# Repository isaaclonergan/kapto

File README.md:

# kapto
Framework to convert a 3D printer into an affordable pick and place machine.

# sammich
Interpreter board for Creality 4.2.7 motherboard. Plugs directly into display port and will convert to RS-485 for the feeder modules.

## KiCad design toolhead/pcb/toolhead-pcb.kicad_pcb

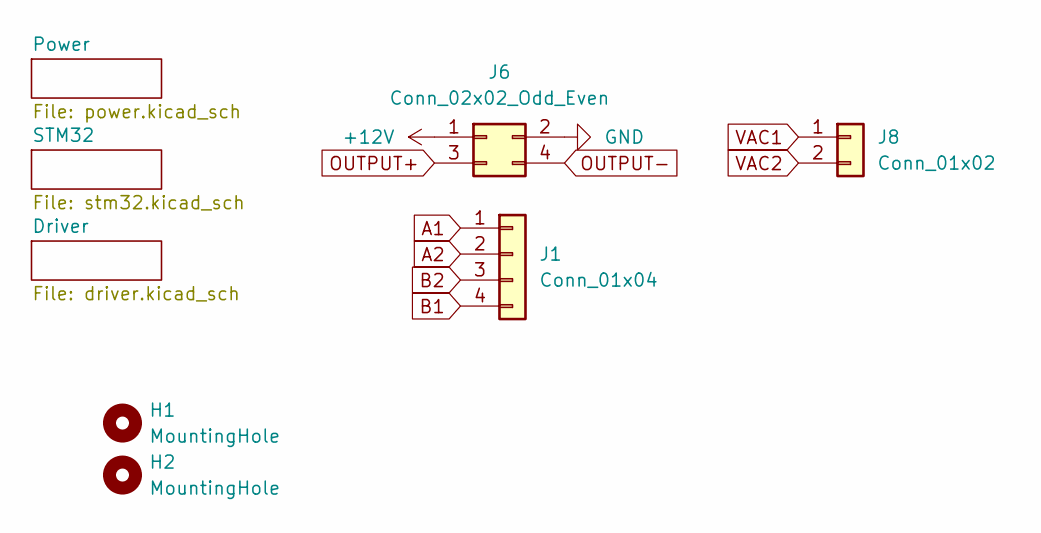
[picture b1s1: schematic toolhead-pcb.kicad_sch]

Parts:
H1, H2: MountingHole; MountingHole_3.2mm_M3
J1: Conn_01x04; JST_XH_B4B-XH-A_1x04_P2.50mm_Vertical
J6: Conn_02x02_Odd_Even; Molex_Micro-Fit_3.0_43045-0400_2x02_P3.00mm_Horizontal
J8: Conn_01x02; JST_XH_B2B-XH-A_1x02_P2.50mm_Vertical

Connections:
+12V: J6.1; also elsewhere on the board
A1: J1.1; also elsewhere on the board
A2: J1.2; also elsewhere on the board
B1: J1.4; also elsewhere on the board
B2: J1.3; also elsewhere on the board
GND: J6.2; also elsewhere on the board
OUTPUT+: J6.3; also elsewhere on the board
OUTPUT-: J6.4; also elsewhere on the board
VAC1: J8.1; also elsewhere on the board
VAC2: J8.2; also elsewhere on the board

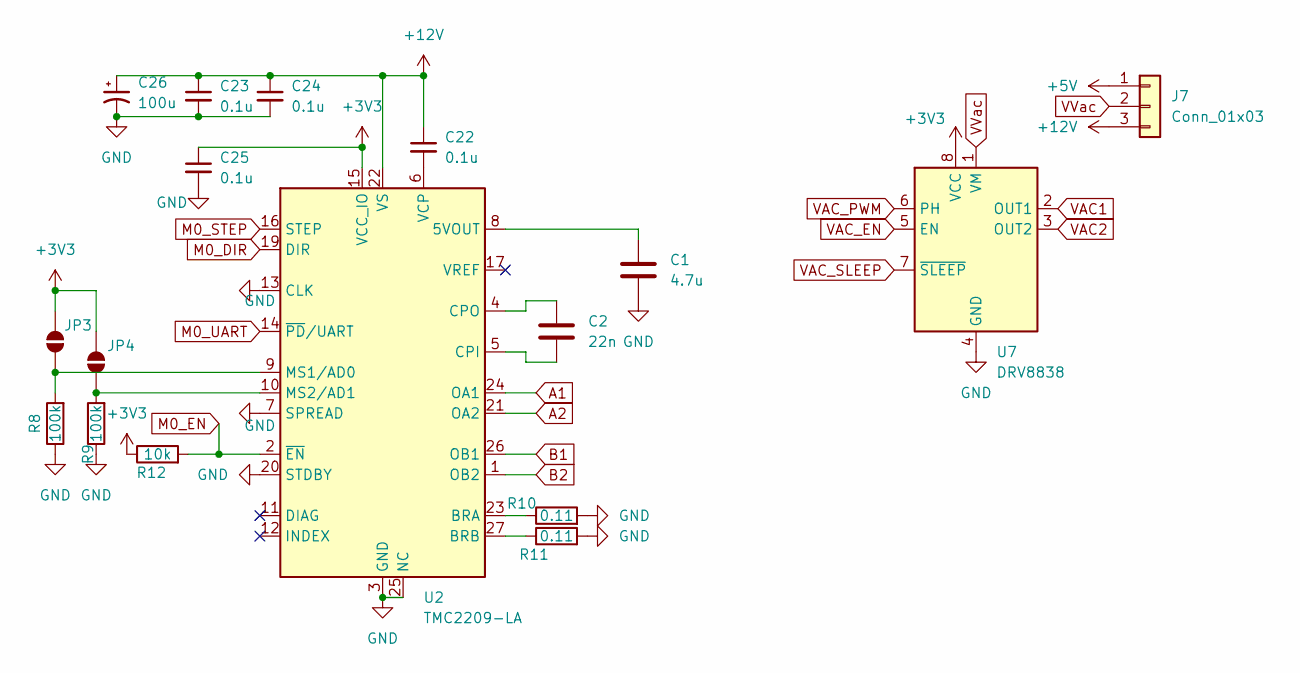
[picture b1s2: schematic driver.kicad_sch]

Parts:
C1: 4.7u; C_0603_1608Metric
C2: 22n; C_0603_1608Metric
C22, C23, C24, C25: 0.1u; C_0603_1608Metric
C26: 100u; CP_Elec_6.3x7.7
J7: Conn_01x03; PinHeader_1x03_P2.54mm_Vertical
JP3, JP4: SolderJumper_2_Open; R_0603_1608Metric
R8, R9: 100k; R_0603_1608Metric
R10, R11: 0.11; R_0603_1608Metric
R12: 10k; R_0603_1608Metric
U2: TMC2209-LA; VQFN-28-1EP_5x5mm_P0.5mm_EP3.7x3.7mm_ThermalVias
U7: DRV8838; WSON-8-1EP_2x2mm_P0.5mm_EP0.9x1.6mm

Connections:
+3V3: C25.1, JP3.2 (B), JP4.2 (B), R12.1, U2.15 (VCC_IO), U7.8 (VCC); also elsewhere on the board
+5V: J7.1; also elsewhere on the board
+12V: C22.1, C23.1, C24.1, C26.1, J7.3, U2.22 (VS), U2.28 (VS); also elsewhere on the board
A1: U2.24 (OA1); also elsewhere on the board
A2: U2.21 (OA2); also elsewhere on the board
B1: U2.26 (OB1); also elsewhere on the board
B2: U2.1 (OB2); also elsewhere on the board
GND: C1.1, C23.2, C24.2, C25.2, C26.2, R8.1, R9.1, R10.2, R11.2, U2.3 (GND), U2.7 (SPREAD), U2.13 (CLK), U2.18 (GND), U2.20 (STDBY), U2.25 (NC), U2.29 (GND), U7.4 (GND), U7.9 (GND); also elsewhere on the board
M0_DIR: U2.19 (DIR); also elsewhere on the board
M0_EN: R12.2, U2.2 (~EN); also elsewhere on the board
M0_STEP: U2.16 (STEP); also elsewhere on the board
M0_UART: U2.14 (~PD/UART); also elsewhere on the board
unnamed: JP3.1 (A), R8.2, U2.9 (MS1/AD0)
unnamed: JP4.1 (A), R9.2, U2.10 (MS2/AD1)
unnamed: C1.2, U2.8 (5VOUT)
unnamed: R10.1, U2.23 (BRA)
unnamed: R11.1, U2.27 (BRB)
unnamed: C2.2, U2.5 (CPI)
unnamed: C2.1, U2.4 (CPO)
unnamed: C22.2, U2.6 (VCP)
VAC1: U7.2 (OUT1); also elsewhere on the board
VAC2: U7.3 (OUT2); also elsewhere on the board
VAC_EN: U7.5 (EN); also elsewhere on the board
VAC_PWM: U7.6 (PH); also elsewhere on the board
VAC_SLEEP: U7.7 (~SLEEP); also elsewhere on the board
VVac: J7.2, U7.1 (VM)

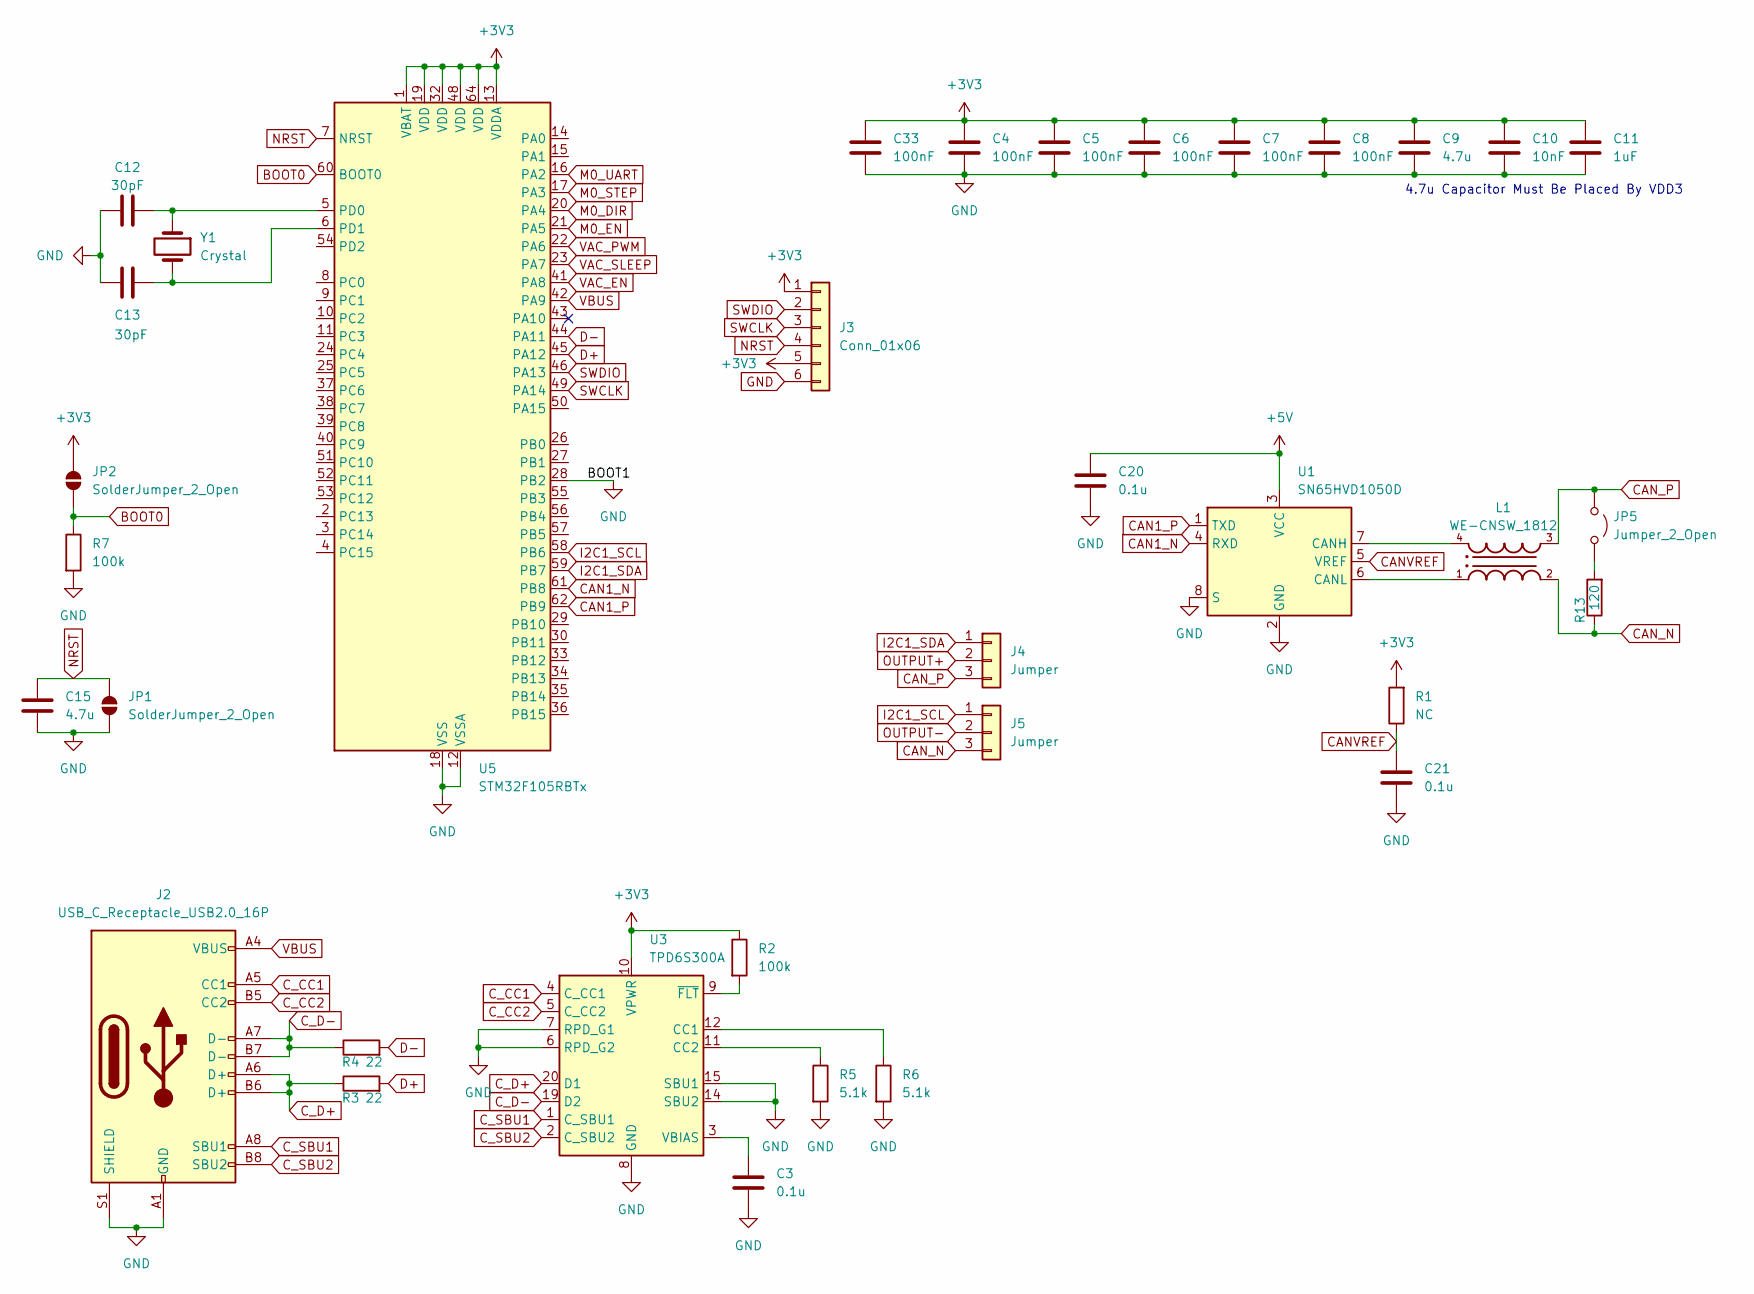
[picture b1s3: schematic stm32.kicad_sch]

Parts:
C3, C20, C21: 0.1u; C_0603_1608Metric
C4, C5, C6, C7, C8, C33: 100nF; C_0603_1608Metric
C9, C15: 4.7u; C_0603_1608Metric
C10: 10nF; C_0603_1608Metric
C11: 1uF; C_0603_1608Metric
C12, C13: 30pF; C_0603_1608Metric
J2: USB_C_Receptacle_USB2.0_16P; USB_C_Receptacle_GCT_USB4105-xx-A_16P_TopMnt_Horizontal
J3: Conn_01x06; PinHeader_1x06_P2.54mm_Vertical
J4, J5: Jumper; PinHeader_1x03_P2.54mm_Vertical
JP1, JP2: SolderJumper_2_Open; SolderJumper-2_P1.3mm_Open_TrianglePad1.0x1.5mm
JP5: Jumper_2_Open; PinHeader_1x02_P2.54mm_Vertical
L1: WE-CNSW_1812; DigiKey_Part_Number 732-7290-1-ND
R1: NC; R_0603_1608Metric
R2, R7: 100k; R_0603_1608Metric
R3, R4: 22; R_0603_1608Metric
R5, R6: 5.1k; R_0603_1608Metric
R13: 120; R_0603_1608Metric
U1: SN65HVD1050D; SOIC-8_3.9x4.9mm_P1.27mm
U3: TPD6S300A; WQFN-20-1EP_3x3mm_P0.4mm_EP1.7x1.7mm_ThermalVias
U5: STM32F105RBTx; LQFP-64_10x10mm_P0.5mm
Y1: Crystal; Crystal_SMD_Abracon_ABM7-2Pin_6.0x3.5mm

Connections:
+3V3: C4.1, C5.1, C6.1, C7.1, C8.1, C9.1, C10.1, C11.1, C33.1, J3.1, J3.5, JP2.2 (B), R1.2, R2.1, U3.10 (VPWR), U5.1 (VBAT), U5.13 (VDDA), U5.19 (VDD), U5.32 (VDD), U5.48 (VDD), U5.64 (VDD); also elsewhere on the board
+5V: C20.1, U1.3 (VCC); also elsewhere on the board
BOOT0: JP2.1 (A), R7.1, U5.60 (BOOT0)
CAN1_N: U1.4 (RXD), U5.61 (PB8)
CAN1_P: U1.1 (TXD), U5.62 (PB9)
CANVREF: C21.1, R1.1, U1.5 (VREF)
CAN_N: J5.3, L1.2, R13.1
CAN_P: J4.3, JP5.1 (A), L1.3
C_CC1: J2.A5 (CC1), U3.4 (C_CC1)
C_CC2: J2.B5 (CC2), U3.5 (C_CC2)
C_D+: J2.A6 (D+), J2.B6 (D+), R3.1, U3.20 (D1)
C_D-: J2.A7 (D-), J2.B7 (D-), R4.1, U3.19 (D2)
C_SBU1: J2.A8 (SBU1), U3.1 (C_SBU1)
C_SBU2: J2.B8 (SBU2), U3.2 (C_SBU2)
D+: R3.2, U5.45 (PA12)
D-: R4.2, U5.44 (PA11)
GND: C3.2, C4.2, C5.2, C6.2, C7.2, C8.2, C9.2, C10.2, C11.2, C12.1, C13.1, C15.2, C20.2, C21.2, C33.2, J2.A1 (GND), J2.A12 (GND), J2.B1 (GND), J2.B12 (GND), J2.S1 (SHIELD), J3.6, JP1.1 (A), R5.2, R6.2, R7.2, U1.2 (GND), U1.8 (S), U3.6 (RPD_G2), U3.7 (RPD_G1), U3.8 (GND), U3.13 (GND), U3.14 (SBU2), U3.15 (SBU1), U3.16 (GND), U3.17 (GND), U3.18 (GND), U3.21 (GND), U5.12 (VSSA), U5.18 (VSS), U5.28 (PB2), U5.31 (VSS), U5.47 (VSS), U5.63 (VSS); also elsewhere on the board
I2C1_SCL: J5.1, U5.58 (PB6)
I2C1_SDA: J4.1, U5.59 (PB7)
M0_DIR: U5.20 (PA4); also elsewhere on the board
M0_EN: U5.21 (PA5); also elsewhere on the board
M0_STEP: U5.17 (PA3); also elsewhere on the board
M0_UART: U5.16 (PA2); also elsewhere on the board
NRST: C15.1, J3.4, JP1.2 (B), U5.7 (NRST)
unnamed: JP5.2 (B), R13.2
unnamed: L1.4, U1.7 (CANH)
unnamed: L1.1, U1.6 (CANL)
unnamed: R6.1, U3.12 (CC1)
unnamed: R5.1, U3.11 (CC2)
unnamed: C3.1, U3.3 (VBIAS)
unnamed: R2.2, U3.9 (~FLT)
unnamed: C12.2, U5.5 (PD0), Y1.1
unnamed: C13.2, U5.6 (PD1), Y1.2
OUTPUT+: J4.2; also elsewhere on the board
OUTPUT-: J5.2; also elsewhere on the board
SWCLK: J3.3, U5.49 (PA14)
SWDIO: J3.2, U5.46 (PA13)
VAC_EN: U5.41 (PA8); also elsewhere on the board
VAC_PWM: U5.22 (PA6); also elsewhere on the board
VAC_SLEEP: U5.23 (PA7); also elsewhere on the board
VBUS: J2.A4 (VBUS), J2.A9 (VBUS), J2.B4 (VBUS), J2.B9 (VBUS), U5.42 (PA9); also elsewhere on the board

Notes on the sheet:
4.7u Capacitor Must Be Placed By VDD3

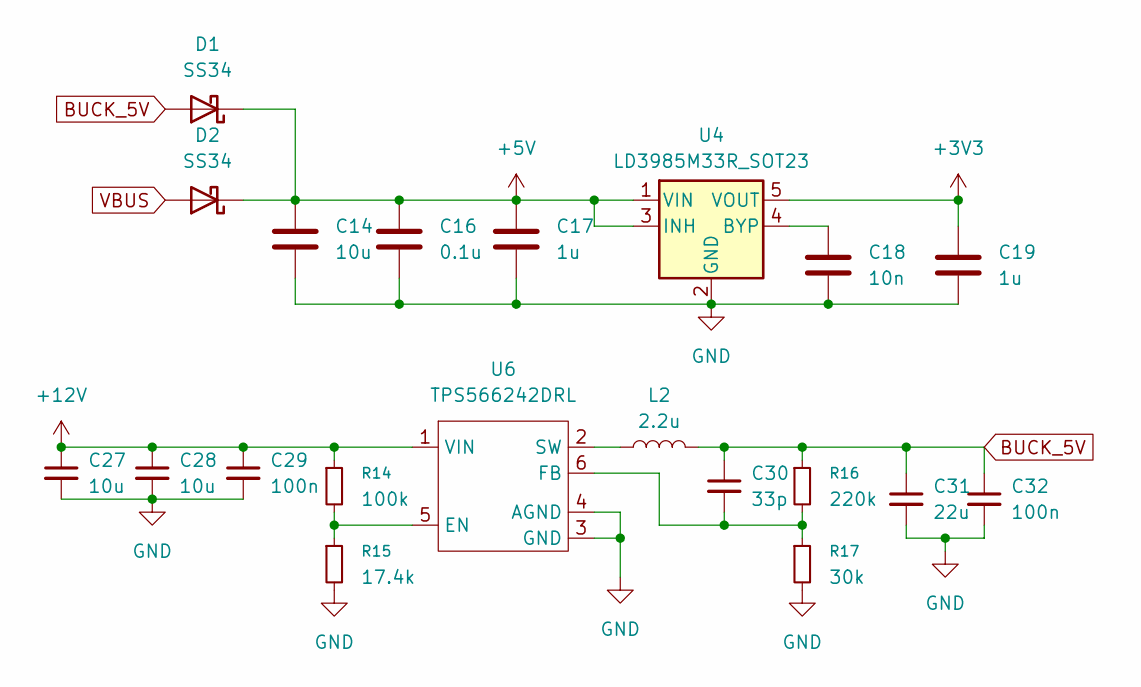
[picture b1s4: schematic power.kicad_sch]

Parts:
C14, C27, C28: 10u; C_0603_1608Metric
C16: 0.1u; C_0603_1608Metric
C17, C19: 1u; C_0603_1608Metric
C18: 10n; C_0603_1608Metric
C29, C32: 100n; C_0603_1608Metric
C30: 33p; C_0603_1608Metric
C31: 22u; C_0603_1608Metric
D1, D2: SS34; D_SMA
L2: 2.2u; IND_XGL4018-222MEC
R14: 100k; R_0603_1608Metric
R15: 17.4k; R_0603_1608Metric
R16: 220k; R_0603_1608Metric
R17: 30k; R_0603_1608Metric
U4: LD3985M33R_SOT23; SOT-23-5
U6: TPS566242DRL; SOT-563

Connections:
+3V3: C19.1, U4.5 (VOUT); also elsewhere on the board
+5V: C14.1, C16.1, C17.1, D1.1 (K), D2.1 (K), U4.1 (VIN), U4.3 (INH); also elsewhere on the board
+12V: C27.1, C28.1, C29.1, R14.1, U6.1 (VIN); also elsewhere on the board
BUCK_5V: C30.1, C31.1, C32.1, D1.2 (A), L2.2, R16.1
GND: C14.2, C16.2, C17.2, C18.2, C19.2, C27.2, C28.2, C29.2, C31.2, C32.2, R15.2, R17.2, U4.2 (GND), U6.3 (GND), U6.4 (AGND); also elsewhere on the board
unnamed: C18.1, U4.4 (BYP)
unnamed: R14.2, R15.1, U6.5 (EN)
unnamed: C30.2, R16.2, R17.1, U6.6 (FB)
unnamed: L2.1, U6.2 (SW)
VBUS: D2.2 (A); also elsewhere on the board

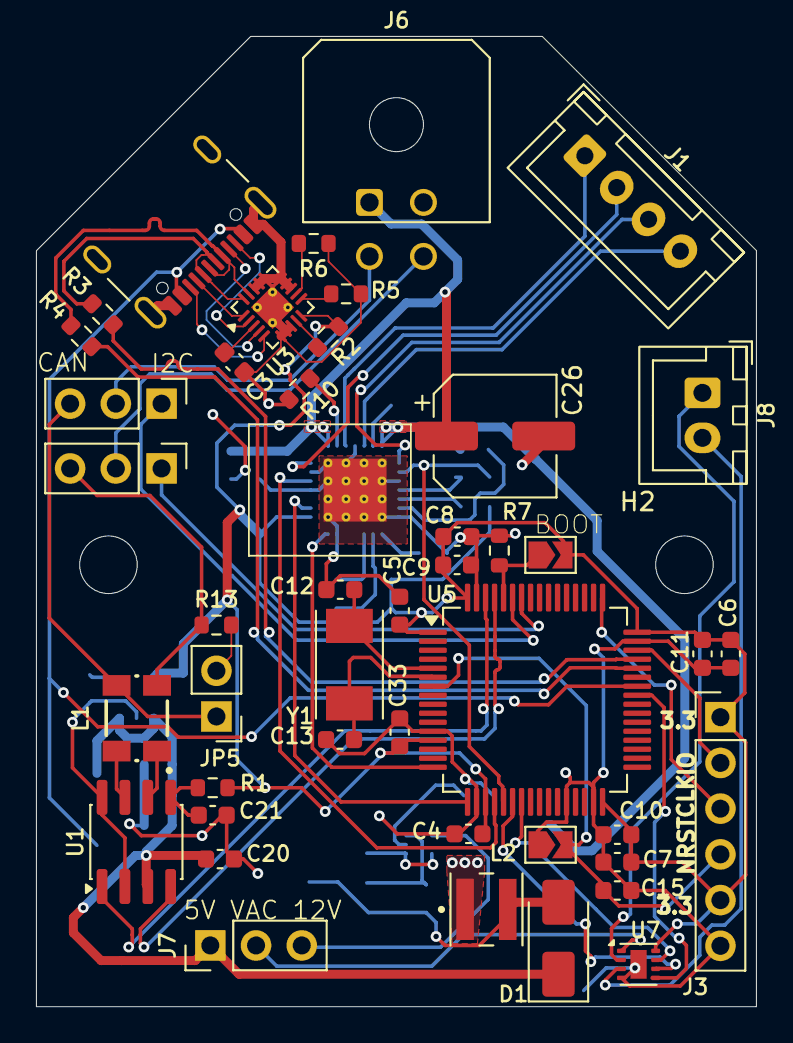
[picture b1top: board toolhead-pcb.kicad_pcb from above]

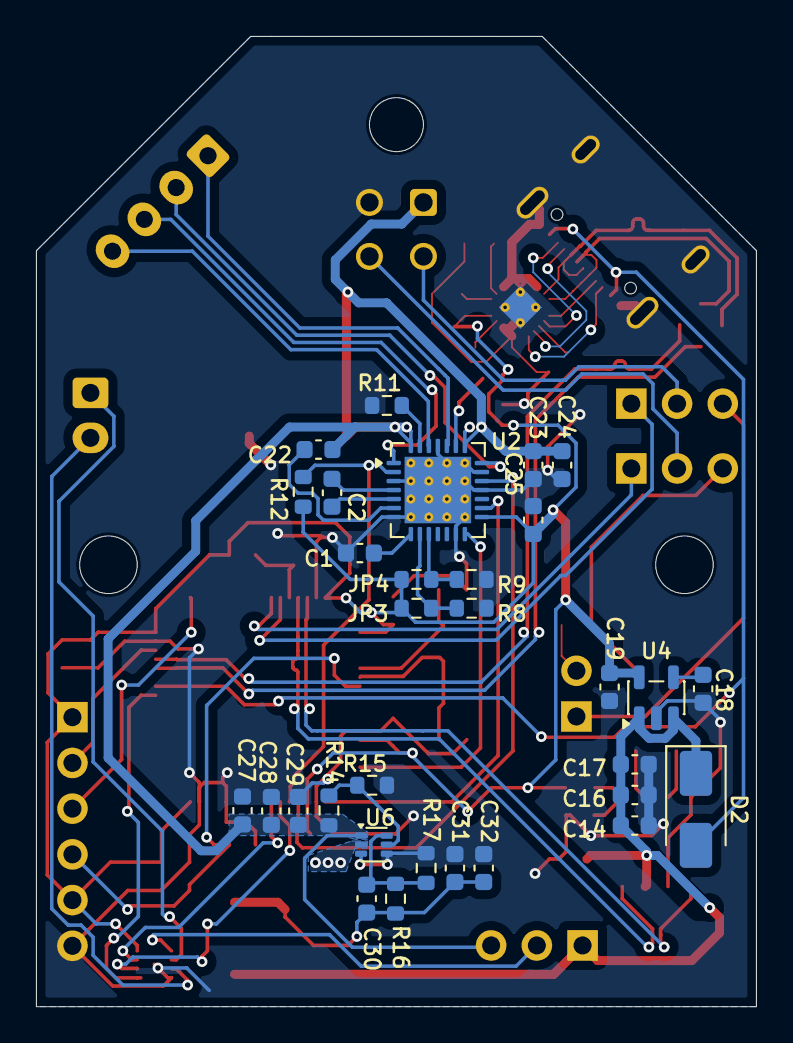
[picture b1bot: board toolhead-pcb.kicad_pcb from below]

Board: 2 copper layers, 40.0 x 53.9 mm, 77 parts (31 on the bottom side), 62 nets.

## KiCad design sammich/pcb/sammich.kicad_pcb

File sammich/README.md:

# Sammich

Sammich is an interpreter that sits between the Creality 4.2.7 board and our feeders and vacuum. It's purporse is to interpret the simpler I2C commands coming from the Creality board into a more complex format for us to use. This board instructs the feeders how far they should advance depending on the loaded component and receives data back from their encoders. A future goal is to enable an automatic addressing for the feeders which would allow for plug and play compatibility.

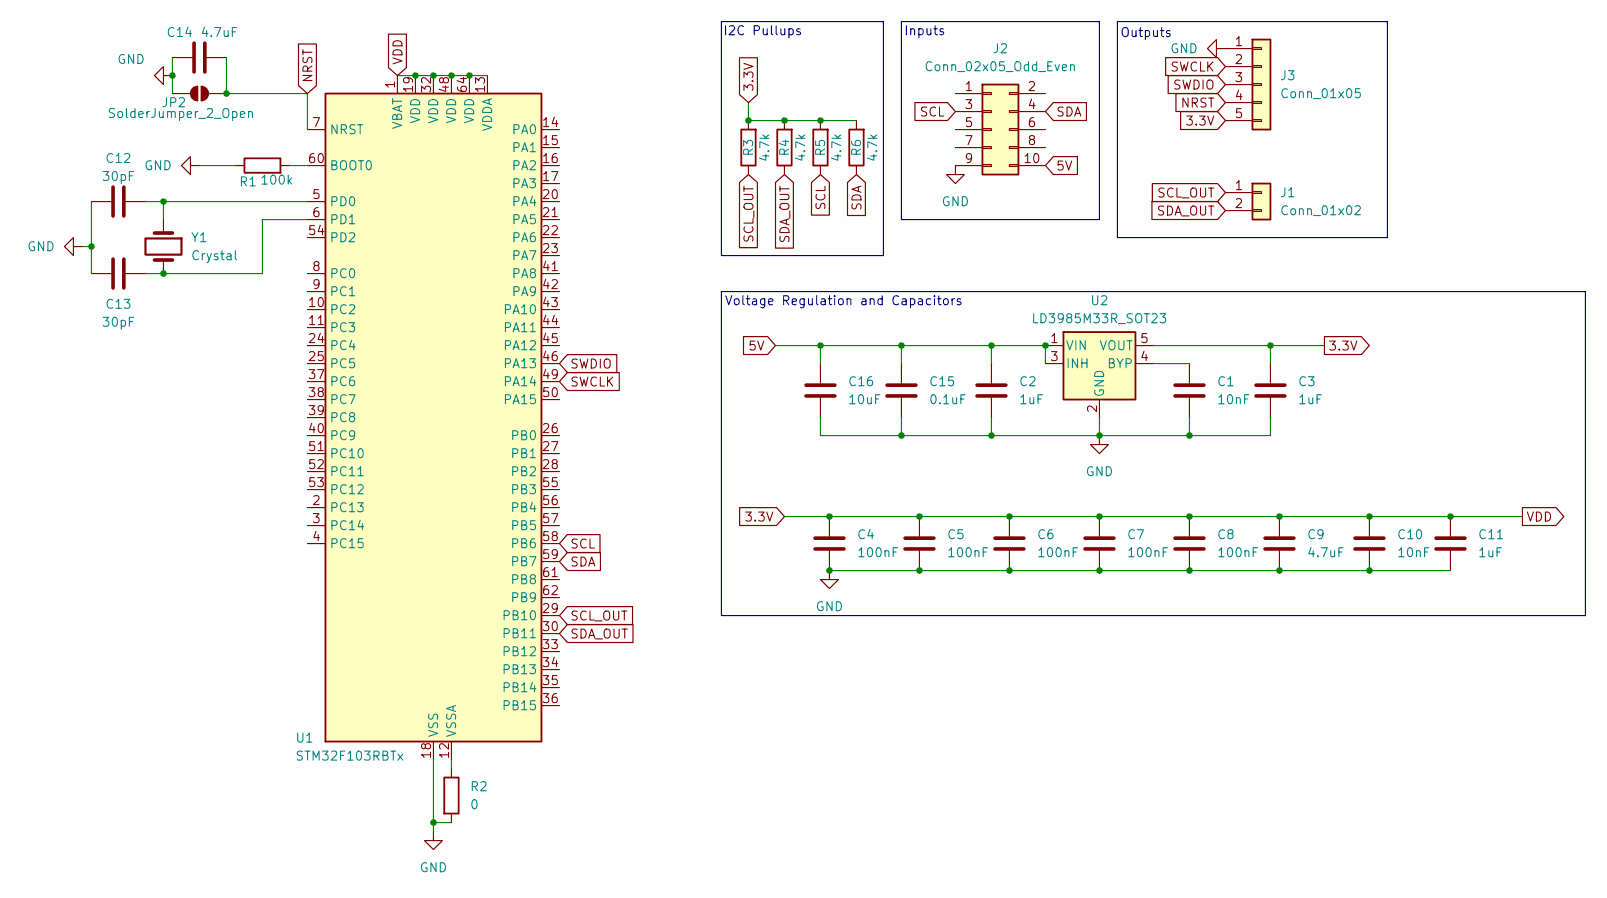
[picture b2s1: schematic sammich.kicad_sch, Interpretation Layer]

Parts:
C1, C10: 10nF; C_0201_0603Metric
C2, C3, C11: 1uF; C_0201_0603Metric
C4, C5, C6, C7, C8: 100nF; C_0201_0603Metric
C9, C14: 4.7uF; C_0201_0603Metric
C12, C13: 30pF; C_0201_0603Metric
C15: 0.1uF; C_0201_0603Metric
C16: 10uF; C_0402_1005Metric
J1: Conn_01x02; JST_XH_S2B-XH-A_1x02_P2.50mm_Horizontal
J2: Conn_02x05_Odd_Even; PinSocket_2x05_P2.54mm_Vertical
J3: Conn_01x05; PinHeader_1x05_P2.54mm_Vertical
JP2: SolderJumper_2_Open; SolderJumper-2_P1.3mm_Open_TrianglePad1.0x1.5mm
R1: 100k; R_0201_0603Metric
R2: 0; R_0201_0603Metric
R3, R4, R5, R6: 4.7k; R_0201_0603Metric
U1: STM32F103RBTx; LQFP-64_10x10mm_P0.5mm
U2: LD3985M33R_SOT23; SOT-23-5
Y1: Crystal; Crystal_SMD_Abracon_ABM7-2Pin_6.0x3.5mm

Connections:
3.3V: C3.1, C4.1, C5.1, C6.1, C7.1, C8.1, C9.1, C10.1, C11.1, J3.5, R3.2, R4.2, R5.2, R6.2, U1.1 (VBAT), U1.13 (VDDA), U1.19 (VDD), U1.32 (VDD), U1.48 (VDD), U1.64 (VDD), U2.5 (VOUT)
5V: C2.1, C15.1, C16.1, J2.10, U2.1 (VIN), U2.3 (INH)
GND: C1.2, C2.2, C3.2, C4.2, C5.2, C6.2, C7.2, C8.2, C9.2, C10.2, C11.2, C12.1, C13.1, C14.1, C15.2, C16.2, J2.9, J3.1, JP2.1 (A), R1.1, R2.2, U1.18 (VSS), U1.31 (VSS), U1.47 (VSS), U1.63 (VSS), U2.2 (GND)
NRST: C14.2, J3.4, JP2.2 (B), U1.7 (NRST)
unnamed: R1.2, U1.60 (BOOT0)
unnamed: C12.2, U1.5 (PD0), Y1.1
unnamed: C13.2, U1.6 (PD1), Y1.2
unnamed: R2.1, U1.12 (VSSA)
unnamed: C1.1, U2.4 (BYP)
SCL: J2.3, R5.1, U1.58 (PB6)
SCL_OUT: J1.1, R3.1, U1.29 (PB10)
SDA: J2.4, R6.1, U1.59 (PB7)
SDA_OUT: J1.2, R4.1, U1.30 (PB11)
SWCLK: J3.2, U1.49 (PA14)
SWDIO: J3.3, U1.46 (PA13)

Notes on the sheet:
Outputs
I2C Pullups
Voltage Regulation and Capacitors
Inputs

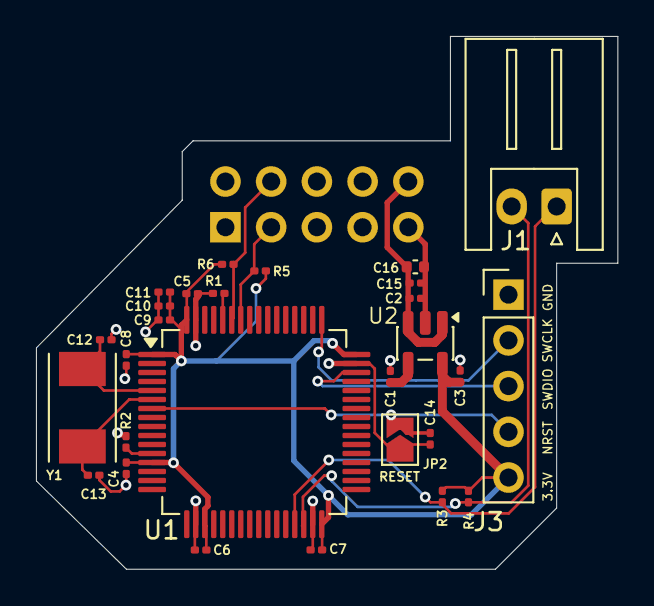
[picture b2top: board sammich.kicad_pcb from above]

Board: 2 copper layers, 32.3 x 29.6 mm, 29 parts (1 on the bottom side), 15 nets.

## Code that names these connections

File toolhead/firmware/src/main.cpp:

<<<<<<< HEAD
#include <Arduino.h>
void setup() {
  pinMode(PB6, OUTPUT);
  pinMode(PB7, OUTPUT);
=======
#include <Wire.h>

// ── TMC2209 Pins ──────────────────────────────────────────────────────────────
#define M0_STEP_PIN     PA3
#define M0_DIR_PIN      PA4
#define M0_EN_PIN       PA5

// ── Motor Constants ───────────────────────────────────────────────────────────
#define STEPS_PER_REV   200
#define MICROSTEPS        8
#define STEP_DELAY_US   500
#define DIR_SETUP_US     20

// ── I2C ───────────────────────────────────────────────────────────────────────
#define I2C_ADDRESS     0x15

// ── Absolute position tracking ────────────────────────────────────────────────
volatile bool    pendingMove      = false;
volatile int16_t pendingTargetDeg = 0;
volatile bool    busy             = false;

int16_t currentPosDeg = 0;   // non-volatile: only touched in loop()

// ─────────────────────────────────────────────────────────────────────────────
// I2C Frame layout:
//   1 byte  → uint8_t  → target absolute position in degrees (0 to 255)
//   2 bytes → int16_t  → target absolute position in degrees (–32768 to +32767)
//             big-endian: byte[0] = high byte, byte[1] = low byte
// ─────────────────────────────────────────────────────────────────────────────
void onReceive(int numBytes) {
  if (numBytes < 1) {
    while (Wire.available()) Wire.read();
    return;
  }

  int16_t targetDeg = 0;

  if (numBytes >= 2) {
    // Two bytes: int16_t, big-endian
    uint8_t hi = Wire.read();
    uint8_t lo = Wire.read();
    targetDeg = (int16_t)((uint16_t)hi << 8 | lo);
  } else {
    // One byte: uint8_t — zero-extend into int16_t (0–255)
    targetDeg = (int16_t)(uint8_t)Wire.read();
  }

  // Drain any unexpected extra bytes
  while (Wire.available()) Wire.read();

  if (!busy) {
    pendingTargetDeg = targetDeg;
    pendingMove      = true;
  }
}

// ─────────────────────────────────────────────────────────────────────────────
void rotateDegrees(float degrees, unsigned int speed_us = STEP_DELAY_US) {
  if (degrees == 0) return;

  digitalWrite(M0_DIR_PIN, degrees > 0 ? LOW : HIGH);
  delayMicroseconds(DIR_SETUP_US);

  if (degrees < 0) degrees = -degrees;

  long steps = lround((degrees / 360.0f) * STEPS_PER_REV * MICROSTEPS);
  for (long i = 0; i < steps; i++) {
    digitalWrite(M0_STEP_PIN, HIGH);
    delayMicroseconds(speed_us);
    digitalWrite(M0_STEP_PIN, LOW);
    delayMicroseconds(speed_us);
  }
}

// ─────────────────────────────────────────────────────────────────────────────
void setup() {
  pinMode(M0_STEP_PIN, OUTPUT);
  pinMode(M0_DIR_PIN,  OUTPUT);
  pinMode(M0_EN_PIN,   OUTPUT);
  digitalWrite(M0_STEP_PIN, LOW);
  digitalWrite(M0_DIR_PIN,  LOW);
  digitalWrite(M0_EN_PIN,   LOW);   // enable TMC2209

  currentPosDeg = 0;                // absolute origin

  Wire.begin(I2C_ADDRESS);
  Wire.onReceive(onReceive);
  Wire.onRequest([]() {
    // Return current position as int16_t big-endian
    Wire.write((uint8_t)(currentPosDeg >> 8));
    Wire.write((uint8_t)(currentPosDeg & 0xFF));
  });
>>>>>>> 3abca72cb1aa715aa9f9f101da244371be92d0be
}

// ─────────────────────────────────────────────────────────────────────────────
void loop() {
<<<<<<< HEAD
  // Turn both ON
  digitalWrite(PB6, HIGH);
  digitalWrite(PB7, HIGH);
  delay(500);

  // Turn both OFF
  digitalWrite(PB7, LOW);
  delay(500);
=======
  if (pendingMove) {
    pendingMove = false;
    busy        = true;

    int16_t target = pendingTargetDeg;
    int16_t delta  = target - currentPosDeg;

    rotateDegrees((float)delta);
    currentPosDeg = target;

    busy = false;
  }
>>>>>>> 3abca72cb1aa715aa9f9f101da244371be92d0be
}

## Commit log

2025-10-03 Added Marlin submodule
2025-10-03 Updated Marlin branch
2025-10-08 Initial I2C support for Creality 4.2.7
2025-10-08 Basic readme
2025-10-08 fixed build process
2025-10-15 Added sammich pcb files
2025-10-15 Updated readmes for firmware and root
2025-11-13 Added test code
2025-11-13 Removed platformio example README
2025-11-13 Updated PCB to use I2C
2025-11-13 removed gitignore
2025-11-13 Added readme
2025-12-02 Initial Camera code
2026-03-23 Initial platformio setup for F105
2026-03-23 Updated code for 8MB flash ESP
2026-03-23 Toolhead pcb
2026-03-23 Added other pages
2026-05-07 Toolhead code finalized
2026-05-07 Added int16_t i2c support; Toolhead to absolute coordinates
2026-05-18 Updated toolhead, camera
2026-05-18 Moved camera firmware
2026-05-18 Removed espcam dir
